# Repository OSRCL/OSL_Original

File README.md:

# Open Source RC Lights
(aka, "OSL")

**--> [INSTRUCTIONS & DOCUMENTATION AVAILABLE HERE](https://openpanzer.org/wiki/doku.php?id=wiki:otherprojects:osl) <--**

OSL is an Arduino-based, open source project for controlling lights in RC cars and trucks. It uses an ATmega328 as the processor and has 8 light outputs. All the components on the board are through-hole which makes it easy to assemble and solder. 
 
Some features: 
  * Control up to 8 light circuits
  * Accepts three channels of RC input (throttle, steering, and an optional 3rd channel)
  * Each light can respond to various model **States**: forward, reverse, stopped, stopped after delay, braking, right turn, left turn, no turn, accelerating, decelerating, and any of up to 5 positions for the channel 3 switch if attached. 
  * For each light in each State the **Setting** defines the behavior of the light: on, off, fade on, fade off, blink, fast blink, safety blink (and the alternate versions of blink, fast blink, and safety blink), soft blink, dim, xenon-on effect, or backfire effect.
  * The collection of all Settings for all lights in all States is called a **Scheme**. Multiple schemes can be defined and you can switch between them from your transmitter.
  * Schemes and other operating adjustments are made in the free Arduino IDE. Everything is well explained and you don't need to know how to write code.
  * Works with both 5 and 6 volt RC systems
<br/>

## Resources  
  * [OSL Wiki](https://openpanzer.org/wiki/doku.php?id=wiki:otherprojects:osl)
  * [RC Groups Discussion Thread](http://www.rcgroups.com/forums/showthread.php?t=1539753)
  * [Complete collection of resources and downloads](https://openpanzer.org/downloads#OSL)
<br/>

## OSL Hardware
**Board version 1.7**  
See the "hardware" folder in this repository for Eagle board files, schematic, and bill of materials. 
  * [Printable Schematic](https://www.openpanzer.org/secure_downloads/osl/eagle/OpenSourceLights_v17_Schematic.pdf) (PDF)
  * [Bill of Materials](https://www.openpanzer.org/secure_downloads/osl/bom/OpenSourceLights_BOM.pdf) (PDF)
  * [Purchase PCBs at OSH Park](https://oshpark.com/shared_projects/kmCzNipk)
  * [Other user designs](https://www.openpanzer.org/forum/index.php?page=osl_other)
<br/>

## Getting Started with Arduino
First you will need to install the Arduino IDE on your computer, [you can download it from here](https://www.arduino.cc/en/software).

Next download the OSL source files (Arduino calls this a "sketch"). Click the green "Clone or Download" button at the top of this page, then select "Download ZIP." 

1. Unzip the download and put the folder named “OpenSourceLights” into your Arduino “Sketches” folder. This may be a location you specified or it may be the default location that Arduino chose when you installed the IDE. If you are unsure where Arduino thinks your Sketches folder is:
   - Open the Arduino IDE
   - Go to File -> Preferences
   - At the top of the popup screen that appears, look at the path under the heading "Sketchbook location". This shows you where your Sketches folder is. 

2. Open the sketch through the IDE or just by clicking on any of the .ino files in the OpenSourceLights folder. Now let's make sure the IDE is setup to compile the project correctly:
   - In the IDE, go to the Tools menu and select Board -> Arduino AVR Boards -> "Arduino Nano." In fact several boards would work, but "Nano" is the easiest to remember.
   - Make sure we have the correct processor selected. Go to Tools -> Processor -> and select "ATmega328P". **Note:** Some users may need to select "Atmega328P (Old Bootloader)" if they have problems loading the sketch onto their device.

3. Compile. This is done by clicking the checkmark button at the top left of the IDE window, or by going to the Sketch menu and clicking "Verify/Compile." The IDE will run for a few moments then give you the results of the compilation at the bottom of the screen. If successful, you are ready to modify the sketch so that it does what you want! Read this page in the OSL Wiki for more information: [Modifying the Sketch](https://openpanzer.org/wiki/doku.php?id=wiki:otherprojects:osl:sketch)

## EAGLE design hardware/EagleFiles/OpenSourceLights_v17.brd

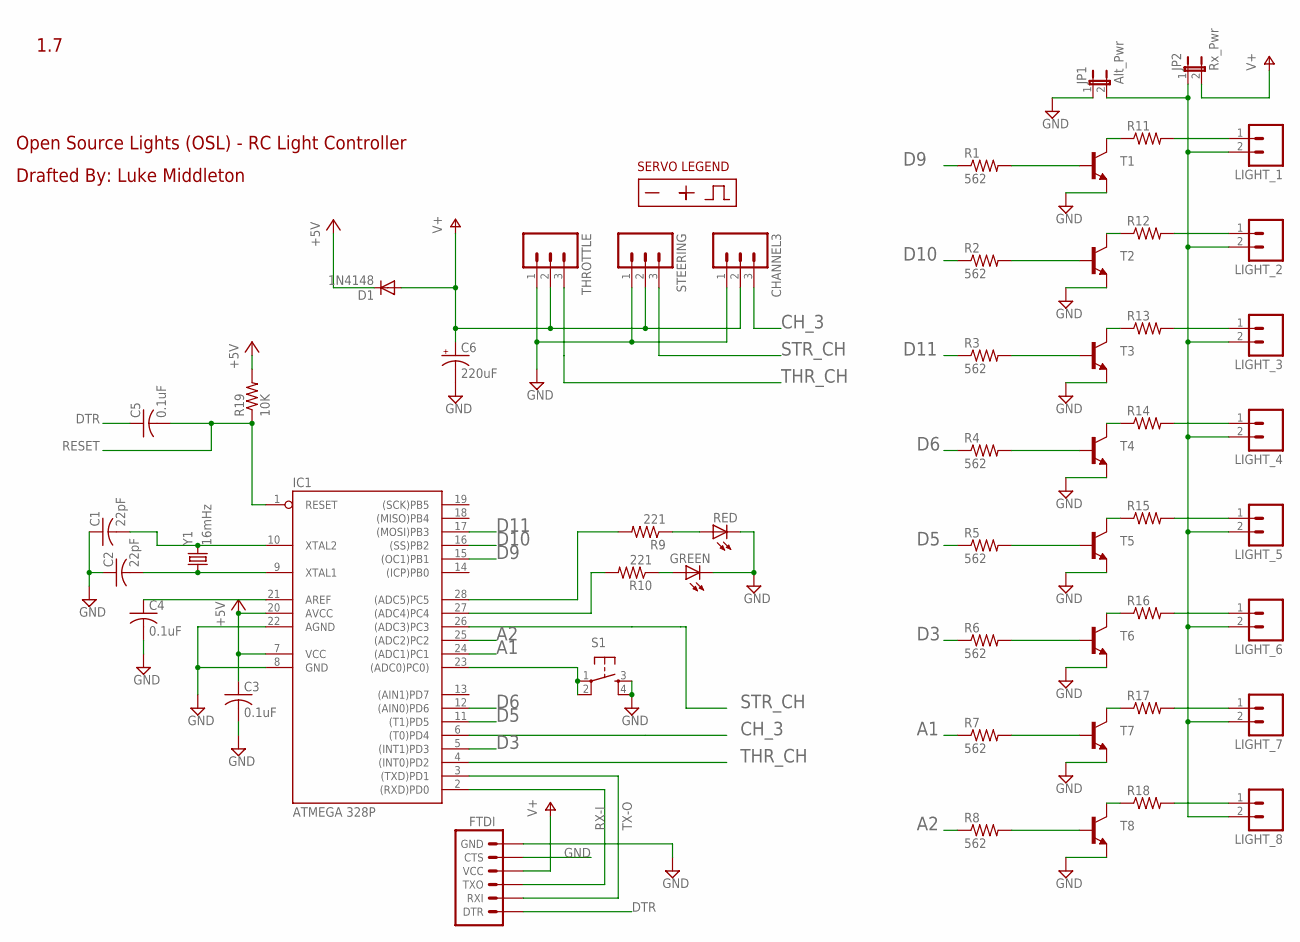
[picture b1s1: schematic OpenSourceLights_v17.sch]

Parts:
C1, C2: 22pF; C025-025X050
C3, C4, C5: 0.1uF; C025-025X050
C6: 220uF; E5-10,5
CHANNEL3: M03LOCK; 1X03_LOCK
D1: 1N4148; DO35-10
FTDI: ARDUINO_SERIAL_PROGRAMLOCK; 1X06_LOCK
GREEN: LED3MM
IC1: ATMEGA 328P; DIL28-3
JP1: Alt_Pwr; 1X02
JP2: Rx_Pwr; SJ_2S-NO
LIGHT_1, LIGHT_2, LIGHT_3, LIGHT_4, LIGHT_5, LIGHT_6, LIGHT_7, LIGHT_8: M02JST-PTH-2_LARGEDRILL; JST-2-PTH+
R1, R2, R3, R4, R5, R6, R7, R8: 562; RESISTOR_VERTICAL
R9, R10: 221; RESISTOR_VERTICAL
R11, R12, R13, R14, R15, R16, R17, R18: RESISTOR; RESISTOR_VERTICAL
R19: 10K; AXIAL-0.4
RED: LED3MM
S1: TAC_SWITCHPTH; TACTILE-PTH
STEERING: M03LOCK; 1X03_LOCK
T1, T2, T3, T4, T5, T6, T7, T8: TRANSISTOR_NPNTH; TO92
THROTTLE: M03LOCK; 1X03_LOCK
U$1: SYMBOLS_SERVONEG_POS_SIG; SYMBOLS_SERVO_REVERSE
Y1: 16mHz; HC49US

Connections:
+5V: C3.1, D1.C, IC1.7 (VCC), IC1.20 (AVCC), R19.P$2 (2)
A1: IC1.24 ((ADC1)PC1), R7.1
A2: IC1.25 ((ADC2)PC2), R8.1
ALTPWR: JP1.2, JP2.1, LIGHT_1.2, LIGHT_2.2, LIGHT_3.2, LIGHT_4.2, LIGHT_5.2, LIGHT_6.2, LIGHT_7.2, LIGHT_8.2
CH_3: CHANNEL3.3, IC1.6 ((T0)PD4)
D3: IC1.5 ((INT1)PD3), R6.1
D5: IC1.11 ((T1)PD5), R5.1
D6: IC1.12 ((AIN0)PD6), R4.1
D9: IC1.15 ((OC1)PB1), R1.1
D10: IC1.16 ((SS)PB2), R2.1
D11: IC1.17 ((MOSI)PB3), R3.1
DTR: C5.1, FTDI.1 (DTR)
GND: C1.1, C2.1, C3.2, C4.2, C6.-, CHANNEL3.1, FTDI.5 (CTS), FTDI.6 (GND), GREEN.K (C), IC1.8 (GND), IC1.22 (AGND), JP1.1, RED.K (C), S1.3, S1.4, STEERING.1, T1.3 (E), T2.3 (E), T3.3 (E), T4.3 (E), T5.3 (E), T6.3 (E), T7.3 (E), T8.3 (E), THROTTLE.1
unnamed: LIGHT_1.1, R11.2
unnamed: LIGHT_2.1, R12.2
unnamed: LIGHT_3.1, R13.2
unnamed: LIGHT_4.1, R14.2
unnamed: LIGHT_5.1, R15.2
unnamed: LIGHT_6.1, R16.2
unnamed: LIGHT_7.1, R17.2
unnamed: LIGHT_8.1, R18.2
unnamed: C1.2, IC1.10 (XTAL2), Y1.2
unnamed: R1.2, T1.2 (B)
unnamed: R2.2, T2.2 (B)
unnamed: R3.2, T3.2 (B)
unnamed: R4.2, T4.2 (B)
unnamed: R5.2, T5.2 (B)
unnamed: R6.2, T6.2 (B)
unnamed: R7.2, T7.2 (B)
unnamed: R8.2, T8.2 (B)
unnamed: C2.2, IC1.9 (XTAL1), Y1.1
unnamed: R11.1, T1.1 (C)
unnamed: R12.1, T2.1 (C)
unnamed: C4.1, IC1.21 (AREF)
unnamed: R13.1, T3.1 (C)
unnamed: R14.1, T4.1 (C)
unnamed: R15.1, T5.1 (C)
unnamed: R16.1, T6.1 (C)
unnamed: R17.1, T7.1 (C)
unnamed: R18.1, T8.1 (C)
unnamed: GREEN.A, R10.1
unnamed: IC1.23 ((ADC0)PC0)), S1.1, S1.2
unnamed: R9.1, RED.A
unnamed: IC1.27 ((ADC4)PC4), R10.2
unnamed: IC1.28 ((ADC5)PC5), R9.2
RESET: C5.2, IC1.1 (RESET), R19.P$1 (1)
RX-I: FTDI.3 (TXO), IC1.2 ((RXD)PD0)
STR_CH: IC1.26 ((ADC3)PC3), STEERING.3
THR_CH: IC1.4 ((INT0)PD2), THROTTLE.3
TX-O: FTDI.2 (RXI), IC1.3 ((TXD)PD1)
V+: C6.+, CHANNEL3.2, D1.A, FTDI.4 (VCC), JP2.2, STEERING.2, THROTTLE.2

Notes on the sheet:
1.7
Drafted By: Luke Middleton
Open Source Lights (OSL) - RC Light Controller

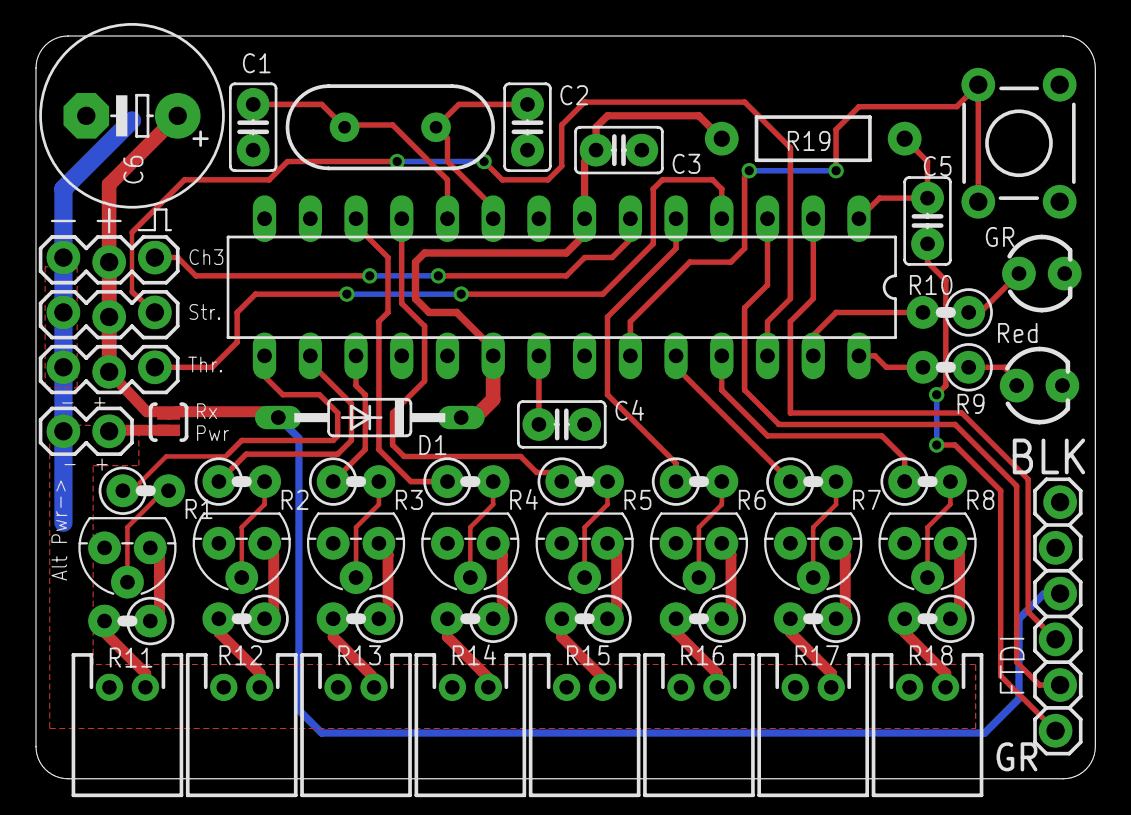
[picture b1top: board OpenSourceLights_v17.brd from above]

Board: 2 copper layers, 58.9 x 41.3 mm, 55 parts (1 on the bottom side), 51 nets.

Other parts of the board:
U$2: SYMBOLS_SERVONEG_POS_SIG; SYMBOLS_SERVO_REVERSE

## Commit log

2016-06-15 Add hardware files
2016-06-15 Forgot to allow temporary turn signal action when just starting to move in reverse.
2016-06-15 Correct drag brake behavior - it should apply when throtlte is at center but vehicle is still moving (DriveModePrev != Stop)
2016-06-15 Add new state - Stop Delay, occurs when stopped for user-specified length of time.
2016-06-15 More Stop Delay
2016-06-17 Double the check time for detecting steering channel and channel 3. These functions only called once during setup.
2016-06-18 Added Nick's Excel file to auto-generate the light setup schemes.
2016-06-19 Updated the light setup Excel utility
2017-06-06 Adjust BLINK and SOFTBLINK to account for the potential that the light should not blink completely OFF but rather only to DIM, depending on the current Channel 3 setting.
2017-06-06 Slight adjustment to default soft blink values, these look a bit better to my eye. Of course the user can adjust them to their own liking.
2017-06-06 Blink changes constitute firmware version 2.10.
2017-08-24 Add compilation note
2018-09-26 Add option to constrain all setings under right & left turn to same conditions as turn signals. See AllTurnSettingsMatch in AA_UserConfig.h. This can be used to create the effect used in some modern 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
2018-10-14 Correct typo that affected the left turn blinker, introduced 9/26/2018
2018-10-14 Update last update date.
2019-01-17 Minor changes to default values.
2019-02-21 Add the option to average (smooth) RC commands if the user enables it on the AA_UserConfig.h file. Thanks to Wombii for code submission, for more see: https://www.rcgroups.com/forums/showthread.php?1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
2019-02-22 Set debug to default to false. The user can change it to whatever they want, but most of the time the onboard LEDs are sufficient for debugging. With recent versions of Arduino the F() macro causes c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
2019-04-29 Add the option to disable blinking external lights on radio signal lost.
2019-06-02 Add a check when changing direction from forward to reverse or vice-versa, and only apply brake if a shift time has been specified or of double-tap reverse is true.
2019-06-02 Further handling of immediate direction changes in cases where that is enabled.
2019-10-18 Fix a bug that affects channel 3 position 5 when channel 3 is reversed. Thanks vk1ajm!
2019-10-21 Increase the speed of the receiver read function by alternating between channels each read. Thanks to wombii.
2019-10-21 Changes by RCGroups user "Wombii" to permit incremental updates of changing light settings instead of their prior blocking update method. Turn signals for example will no operate in sync instead of s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
2019-11-07 Be a bit more lenient on failsafe, only enter if 4 sequential reads have failed. This can help ignore transient glitches. Thank you Wombii.
2021-03-13 Allow steering and channel 3 to be detected even after boot. Fix bug that prevented backfire lights from achieving full brightness (in fact, they were being overwritten by Wombii code which should ha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
2021-03-13 We will also now need new Excel worksheets for those that prefer to use them. "OSL Light Setup_v3.xls" is for OSL firmware versions through 3.xx. It does not know anything about the new "No Turn" sta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
2021-03-13 Wombii wrote the Xenon effect such that when turned off, the light fades off instead of turns off immediately. This is probably an improvement and we are leaving it as is, but a comment is provided h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
2021-04-04 Complete rewrite. Interrupt-based radio reading, asynchronous light settings, simplified user configuration, intergrated libraries.
2021-04-04 Update Settings.
2021-04-04 Fix typo.
2021-04-08 Rearrange settings in UserConfig for a more logical progression.
2021-04-08 Rename AA_LIGHT_SETUP to AA_LightSetup
2021-04-08 Baudrate doesn't need to be a user setting, stick in OSL_Settings.h. We added some stuff to help us print a light scheme for debugging purposes.
2021-04-08 Doesn't make sense to have change scheme mode timing related to turn signals, changed. Also moved some embedded constants to #defines.
2021-04-08 We can now print a clean-looking full scheme and it will look exactly the same as in code.
2021-04-08 Libraries are now in the subfolder "src"
2021-04-08 Default debugging to false.
2021-04-08 Clean up trailing spaces.
2021-04-08 More cleanup
2021-04-09 Update the Excel utility
2021-05-30 If the light was previously in the dim state and we set it to blinking, we don't want it to blink from off to on, but rather from dim to on. Here we correct that. Note, this does not apply to SoftBli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
2021-06-02 Fix minor bug in the Excel tool.
2023-11-08 Certain light settings might not be restored after loss of radio signal, this has been corrected.
2024-03-21 Update ReadMe to mention alternate versions of blink and fast blink.
2024-03-25 Add alternate versions of blink and fast blink, called BLINK_ALT and FASTBLINK_ALT. These will blink at the same defined rate as their existing counterparts, but in an alternating fashion. For exampl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
2025-05-24 Add "Safety Blink" functionality. Two Settings, "SAFETYBLINK" and "SAFETYBLINK_ALT" are provided, along with customized settings on the AA_UserConfig tab, to define a series of blinks (number and fre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
2025-05-24 Clarify note.
2025-05-24 Update README.
